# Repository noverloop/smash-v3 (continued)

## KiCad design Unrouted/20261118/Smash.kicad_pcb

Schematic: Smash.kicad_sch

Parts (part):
CBAT1, CBAT2: 100uF; Capacitor_Tantalum_SMD_CP_EIA-7343-15_Kemet-W; MPN T528W 100uF (7343-15 thinnest variant)
CBAT3: 1uF; Capacitor_SMD_C_0805_2012Metric; MPN C-Series MIL-PRF-32535 X7R 0805 1uF
CBOOST_IN1_1, CBOOST_IN1_2, CBOOST_IN1_3, CBOOST_IN1_4, CBOOST_IN1_5: 2.2uF; Capacitor_SMD_C_0603_1608Metric; MPN C-Series MIL-PRF-32535 X7R 0603 2.2uF
CBOOST_IN2: 100nF; Capacitor_SMD_C_0402_1005Metric; MPN C0402 X7R 100nF
CBOOST_OUT1: 22uF; Capacitor_Tantalum_SMD_CP_EIA-3528-12_Kemet-T; MPN T491T 22uF (3528-12 thinnest variant)
CBOOST_OUT2: 100nF; Capacitor_SMD_C_0402_1005Metric; MPN C0402 X7R 100nF
CMAIN_HOLD1: 100nF; Capacitor_SMD_C_0402_1005Metric; MPN C0402 X7R 100nF
COUT1, COUT2: 22uF; Capacitor_Tantalum_SMD_CP_EIA-3528-12_Kemet-T; MPN T491T 22uF (3528-12 thinnest variant)
COUT3: 100nF; Capacitor_SMD_C_0402_1005Metric; MPN C0402 X7R 100nF
C_ACTIVATE_COMP1: 220nF; Capacitor_SMD_C_0603_1608Metric; MPN C-Series MIL-PRF-32535 X7R 0603 220nF
C_ACTIVATE_IN_1, C_ACTIVATE_IN_2, C_ACTIVATE_IN_3, C_ACTIVATE_IN_4, C_ACTIVATE_IN_5: 2.2uF; Capacitor_SMD_C_0603_1608Metric; MPN C-Series MIL-PRF-32535 X7R 0603 2.2uF
C_ACTIVATE_OUT_1, C_ACTIVATE_OUT_2: 2.2uF; Capacitor_SMD_C_0603_1608Metric; MPN C-Series MIL-PRF-32535 X7R 0603 2.2uF
C_ACTIVATE_SS1: 47nF; Capacitor_SMD_C_0402_1005Metric; MPN C0402 X7R 47nF
C_ANTSW_S1_VDD1: 100nF; Capacitor_SMD_C_0402_1005Metric; MPN C0402 X7R 100nF
C_ANT_S1_DCBLK1: 100pF; Capacitor_SMD_C_0402_1005Metric; MPN TBD 0402 C0G/NP0 100pF (as placed; conf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
C_ANT_S4_MATCH1: 0.5pF; Capacitor_SMD_C_0402_1005Metric; MPN TBD 0402 C0G/NP0 0.5pF (as placed; conf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
C_AON_IN1: 1uF; Capacitor_SMD_C_0805_2012Metric; MPN C-Series MIL-PRF-32535 X7R 0805 1uF
C_AON_OUT1: 1uF; Capacitor_SMD_C_0805_2012Metric; MPN C-Series MIL-PRF-32535 X7R 0805 1uF
C_AWR_1V2_1, C_AWR_1V3_1: 22uF; Capacitor_Tantalum_SMD_CP_EIA-3528-12_Kemet-T; MPN T491T 22uF (3528-12 thinnest variant)
C_AWR_1V2_2, C_AWR_1V3_2, C_AWR_1V8_2, C_AWR_14APLL1, C_AWR_14SYNTH1: 100nF; Capacitor_SMD_C_0402_1005Metric; MPN C0402 X7R 100nF
C_AWR_1V8_1_1, C_AWR_1V8_1_2, C_AWR_1V8_1_3, C_AWR_1V8_1_4, C_AWR_1V8_1_5: 2.2uF; Capacitor_SMD_C_0603_1608Metric; MPN C-Series MIL-PRF-32535 X7R 0603 2.2uF
C_AWR_BUCK_IN1_1, C_AWR_BUCK_IN1_2, C_AWR_BUCK_IN1_3, C_AWR_BUCK_IN1_4, C_AWR_BUCK_IN1_5: 2.2uF; Capacitor_SMD_C_0603_1608Metric; MPN C-Series MIL-PRF-32535 X7R 0603 2.2uF
C_AWR_BUCK_IN2: 100nF; Capacitor_SMD_C_0402_1005Metric; MPN C0402 X7R 100nF
C_AWR_CLKM1: 100pF; Capacitor_SMD_C_0603_1608Metric; MPN SQCSVA 100pF
C_AWR_FLASH_VCC1: 100nF; Capacitor_SMD_C_0402_1005Metric; MPN C0402 X7R 100nF
C_AWR_NRST1: 100nF; Capacitor_SMD_C_0402_1005Metric; MPN C0402 X7R 100nF
C_AWR_OSC_VDD1: 100nF; Capacitor_SMD_C_0402_1005Metric; MPN C0402 X7R 100nF
C_AWR_VBGAP1: 100nF; Capacitor_SMD_C_0402_1005Metric; MPN C0402 X7R 100nF
C_AWR_VOUT_PA1: 100nF; Capacitor_SMD_C_0402_1005Metric; MPN C0402 X7R 100nF
C_BAT_BULK1, C_BAT_BULK2: 470uF; Capacitor_Tantalum_SMD_CP_EIA-7343-15_Kemet-W; MPN T528W 470uF (7343-15 thinnest variant)
C_BLE_DCBLK1: 100pF; Capacitor_SMD_C_0402_1005Metric; MPN TBD 0402 C0G/NP0 100pF (as placed; conf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
C_BOOST_COMP1: 220nF; Capacitor_SMD_C_0603_1608Metric; MPN C-Series MIL-PRF-32535 X7R 0603 220nF
C_BOOST_OUT1: 47uF; Capacitor_Tantalum_SMD_CP_EIA-7343-15_Kemet-W; MPN T528W 47uF (7343-15 thinnest variant)
C_BOOST_OUT2_1, C_BOOST_OUT2_2, C_BOOST_OUT2_3, C_BOOST_OUT2_4, C_BOOST_OUT2_5: 2.2uF; Capacitor_SMD_C_0603_1608Metric; MPN C-Series MIL-PRF-32535 X7R 0603 2.2uF
C_BOOST_OUT3: 100nF; Capacitor_SMD_C_0402_1005Metric; MPN C0402 X7R 100nF
C_BOOST_SS1: 47nF; Capacitor_SMD_C_0402_1005Metric; MPN C0402 X7R 47nF
C_CAM_LDO_VAA_IN1: 1uF; Capacitor_SMD_C_0805_2012Metric; MPN C-Series MIL-PRF-32535 X7R 0805 1uF
C_CAM_LDO_VAA_OUT_1, C_CAM_LDO_VAA_OUT_2: 2.2uF; Capacitor_SMD_C_0603_1608Metric; MPN C-Series MIL-PRF-32535 X7R 0603 2.2uF
C_CAM_LDO_VDD_IN1: 1uF; Capacitor_SMD_C_0805_2012Metric; MPN C-Series MIL-PRF-32535 X7R 0805 1uF
C_CAM_LDO_VDD_OUT1: 2.2uF; Capacitor_SMD_C_0603_1608Metric; MPN C-Series MIL-PRF-32535 X7R 0603 2.2uF
C_CAM_PHY_REG1: 1uF; Capacitor_SMD_C_0805_2012Metric; MPN C-Series MIL-PRF-32535 X7R 0805 1uF
C_CAM_VAA_1: 100nF; Capacitor_SMD_C_0402_1005Metric; MPN C0402 X7R 100nF
C_CAM_VAA_BULK1: 1uF; Capacitor_SMD_C_0805_2012Metric; MPN C-Series MIL-PRF-32535 X7R 0805 1uF
C_CAM_VDD1: 100nF; Capacitor_SMD_C_0402_1005Metric; MPN C0402 X7R 100nF
C_CAM_VDDIO_1: 100nF; Capacitor_SMD_C_0402_1005Metric; MPN C0402 X7R 100nF
C_CAM_VDDIO_BULK1: 1uF; Capacitor_SMD_C_0805_2012Metric; MPN C-Series MIL-PRF-32535 X7R 0805 1uF
C_CAM_VDD_1: 100nF; Capacitor_SMD_C_0402_1005Metric; MPN C0402 X7R 100nF
C_CAM_VDD_BULK1: 1uF; Capacitor_SMD_C_0805_2012Metric; MPN C-Series MIL-PRF-32535 X7R 0805 1uF
C_CAN_GW1: 100nF; Capacitor_SMD_C_0402_1005Metric; MPN C0402 X7R 100nF
C_COMP_PZ1: 100nF; Capacitor_SMD_C_0402_1005Metric; MPN C0402 X7R 100nF
C_DDR_BULK1_1, C_DDR_BULK1_2, C_DDR_BULK1_3, C_DDR_BULK1_4, C_DDR_BULK1_5, C_DDR_BULK2_1, C_DDR_BULK2_2, C_DDR_BULK2_3, C_DDR_BULK2_4, C_DDR_BULK2_5: 2.2uF; Capacitor_SMD_C_0603_1608Metric; MPN C-Series MIL-PRF-32535 X7R 0603 2.2uF
C_DDR_VDD1, C_DDR_VDD2, C_DDR_VDD3, C_DDR_VDD4, C_DDR_VDD5, C_DDR_VDD6: 100nF; Capacitor_SMD_C_0402_1005Metric; MPN C0402 X7R 100nF
C_DDR_VPP1: 1uF; Capacitor_SMD_C_0805_2012Metric; MPN C-Series MIL-PRF-32535 X7R 0805 1uF
C_DDR_VPP2: 100nF; Capacitor_SMD_C_0402_1005Metric; MPN C0402 X7R 100nF
C_DDR_VREFCA1: 100nF; Capacitor_SMD_C_0402_1005Metric; MPN C0402 X7R 100nF
C_FIN1_DVDD1, C_FIN2_DVDD1, C_FIN3_DVDD1, C_FIN4_DVDD1: 1uF; Capacitor_SMD_C_0805_2012Metric; MPN C-Series MIL-PRF-32535 X7R 0805 1uF
C_FIN1_VM1, C_FIN2_VM1, C_FIN3_VM1, C_FIN4_VM1: 100nF; Capacitor_SMD_C_0402_1005Metric; MPN C0402 X7R 100nF
C_FIN_VM_BULK_1, C_FIN_VM_BULK_2, C_FIN_VM_BULK_3, C_FIN_VM_BULK_4, C_FIN_VM_BULK_5: 2.2uF; Capacitor_SMD_C_0603_1608Metric; MPN C-Series MIL-PRF-32535 X7R 0603 2.2uF
C_FIN_VREF1: 100nF; Capacitor_SMD_C_0402_1005Metric; MPN C0402 X7R 100nF
C_G0B1_FIN_BULK1: 1uF; Capacitor_SMD_C_0805_2012Metric; MPN C-Series MIL-PRF-32535 X7R 0805 1uF
C_G0B1_FIN_NRST1, C_G0B1_FIN_VDD1, C_G0B1_FIN_VDD2, C_G0B1_FIN_VREF1: 100nF; Capacitor_SMD_C_0402_1005Metric; MPN C0402 X7R 100nF
C_HACC1: 100nF; Capacitor_SMD_C_0402_1005Metric; MPN C0402 X7R 100nF
C_HACC2_1, C_HACC2_2, C_HACC2_3, C_HACC2_4, C_HACC2_5: 2.2uF; Capacitor_SMD_C_0603_1608Metric; MPN C-Series MIL-PRF-32535 X7R 0603 2.2uF
C_IMU1_1, C_IMU2_1, C_IMU3_1: 100nF; Capacitor_SMD_C_0402_1005Metric; MPN C0402 X7R 100nF
C_IMU1_2, C_IMU2_2, C_IMU3_2: 2.2uF; Capacitor_SMD_C_0603_1608Metric; MPN C-Series MIL-PRF-32535 X7R 0603 2.2uF
C_IMU1_3, C_IMU2_3, C_IMU3_3: 10nF; Capacitor_SMD_C_0402_1005Metric; MPN C0402 X7R 10nF
C_IR_TX1: 1uF; Capacitor_SMD_C_0805_2012Metric; MPN C-Series MIL-PRF-32535 X7R 0805 1uF
C_IR_WAKE1: 10nF; Capacitor_SMD_C_0402_1005Metric; MPN C0402 X7R 10nF
C_J_HALL_FIN_VCC1: 100nF; Capacitor_SMD_C_0402_1005Metric; MPN C0402 X7R 100nF
C_LR_BULK_1, C_LR_BULK_2: 2.2uF; Capacitor_SMD_C_0603_1608Metric; MPN C-Series MIL-PRF-32535 X7R 0603 2.2uF
C_LR_DTC1_VDD1, C_LR_DTC2_VDD1: 100nF; Capacitor_SMD_C_0402_1005Metric; MPN C0402 X7R 100nF
C_LR_HF_ANTBLK1: 100pF; Capacitor_SMD_C_0402_1005Metric; MPN TBD 0402 C0G/NP0 100pF (as placed; conf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
C_LR_HF_RX1: 0.8pF; Capacitor_SMD_C_0402_1005Metric; MPN TBD 0402 C0G/NP0 0.8pF (as placed; conf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
C_LR_HF_RXBLK1: 100pF; Capacitor_SMD_C_0402_1005Metric; MPN TBD 0402 C0G/NP0 100pF (as placed; conf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
C_LR_HF_TX1: 1.2pF; Capacitor_SMD_C_0402_1005Metric; MPN TBD 0402 C0G/NP0 1.2pF (as placed; conf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
C_LR_HF_TX2: 1.0pF; Capacitor_SMD_C_0402_1005Metric; MPN TBD 0402 C0G/NP0 1.0pF (as placed; conf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
C_LR_HF_TXBLK1: 100pF; Capacitor_SMD_C_0402_1005Metric; MPN TBD 0402 C0G/NP0 100pF (as placed; conf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
C_LR_IFSW_VDD1: 100nF; Capacitor_SMD_C_0402_1005Metric; MPN C0402 X7R 100nF
C_LR_SW_HF_VDD1: 100nF; Capacitor_SMD_C_0402_1005Metric; MPN C0402 X7R 100nF
C_LR_TCXO_AC1: 10pF; Capacitor_SMD_C_0402_1005Metric; MPN TBD 0402 C0G/NP0 10pF (as placed; confi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
C_LR_VBAT1: 100nF; Capacitor_SMD_C_0402_1005Metric; MPN C0402 X7R 100nF
C_LR_VDCC1, C_LR_VDCC2: 1uF; Capacitor_SMD_C_0805_2012Metric; MPN C-Series MIL-PRF-32535 X7R 0805 1uF
C_LR_VPAX1, C_LR_VPAX2: 2.2uF; Capacitor_SMD_C_0603_1608Metric; MPN C-Series MIL-PRF-32535 X7R 0603 2.2uF
C_LR_VRPA1: 1nF; Capacitor_SMD_C_0402_1005Metric; MPN C0402 X7R 1nF
C_LR_VTCXO1: 100nF; Capacitor_SMD_C_0402_1005Metric; MPN C0402 X7R 100nF
C_MAG1: 100nF; Capacitor_SMD_C_0402_1005Metric; MPN C0402 X7R 100nF
C_MAG2: 1uF; Capacitor_SMD_C_0805_2012Metric; MPN C-Series MIL-PRF-32535 X7R 0805 1uF
C_MAG_C1: 220nF; Capacitor_SMD_C_0603_1608Metric; MPN C-Series MIL-PRF-32535 X7R 0603 220nF
C_MAG_SHELF1: 100nF; Capacitor_SMD_C_0402_1005Metric; MPN C0402 X7R 100nF
C_MAG_WAKE1: 100nF; Capacitor_SMD_C_0402_1005Metric; MPN C0402 X7R 100nF
C_MPU_0V82_1, C_MPU_0V82_2, C_MPU_5V2, C_MPU_18A_1, C_MPU_18A_2, C_MPU_33b1: 100nF; Capacitor_SMD_C_0402_1005Metric; MPN C0402 X7R 100nF
C_MPU_0V82_BULK1, C_MPU_5V_1, C_MPU_5V_2, C_MPU_5V_3, C_MPU_5V_4, C_MPU_5V_5, C_MPU_33_1, C_MPU_33_2, C_MPU_33_3, C_MPU_33_4, C_MPU_33_5: 2.2uF; Capacitor_SMD_C_0603_1608Metric; MPN C-Series MIL-PRF-32535 X7R 0603 2.2uF
C_MPU_DDR_ZQ1: 0.1uF; Capacitor_SMD_C_0402_1005Metric; MPN C0402 X7R 0.1uF
C_MPU_HSE_VDD1: 100nF; Capacitor_SMD_C_0402_1005Metric; MPN C0402 X7R 100nF
C_MPU_LSE_VDD1: 100nF; Capacitor_SMD_C_0402_1005Metric; MPN C0402 X7R 100nF
C_MPU_NRST1: 100nF; Capacitor_SMD_C_0402_1005Metric; MPN C0402 X7R 100nF
C_MPU_QDDR_1, C_MPU_QDDR_2: 100nF; Capacitor_SMD_C_0402_1005Metric; MPN C0402 X7R 100nF
C_MPU_V08CAP1: 2.2uF; Capacitor_SMD_C_0603_1608Metric; MPN C-Series MIL-PRF-32535 X7R 0603 2.2uF
C_NAND_A_BULK1: 1uF; Capacitor_SMD_C_0805_2012Metric; MPN C-Series MIL-PRF-32535 X7R 0805 1uF
C_NAND_A_VCC1: 100nF; Capacitor_SMD_C_0402_1005Metric; MPN C0402 X7R 100nF
C_NAND_B_BULK1: 1uF; Capacitor_SMD_C_0805_2012Metric; MPN C-Series MIL-PRF-32535 X7R 0805 1uF
C_NAND_B_VCC1: 100nF; Capacitor_SMD_C_0402_1005Metric; MPN C0402 X7R 100nF
C_PMIC_0V9_1, C_PMIC_0V82_1, C_PMIC_1V8_1, C_PMIC_3V3_1: 22uF; Capacitor_Tantalum_SMD_CP_EIA-3528-12_Kemet-T; MPN T491T 22uF (3528-12 thinnest variant)
C_PMIC_0V9_2, C_PMIC_0V82_2, C_PMIC_1V2_2, C_PMIC_1V8_2, C_PMIC_2V8_2, C_PMIC_3V3_2: 100nF; Capacitor_SMD_C_0402_1005Metric; MPN C0402 X7R 100nF
C_PMIC_1V2_1_1, C_PMIC_1V2_1_2, C_PMIC_1V2_1_3, C_PMIC_1V2_1_4, C_PMIC_1V2_1_5, C_PMIC_2V8_1_1, C_PMIC_2V8_1_2, C_PMIC_5V_FILT_1, C_PMIC_5V_FILT_2, C_PMIC_5V_FILT_3, C_PMIC_5V_FILT_4, C_PMIC_5V_FILT_5: 2.2uF; Capacitor_SMD_C_0603_1608Metric; MPN C-Series MIL-PRF-32535 X7R 0603 2.2uF
C_PMIC_INTLDO_1, C_PMIC_INTLDO_2: 2.2uF; Capacitor_SMD_C_0603_1608Metric; MPN C-Series MIL-PRF-32535 X7R 0603 2.2uF
C_PMIC_LDO1, C_PMIC_LDO2, C_PMIC_LDO4, C_PMIC_LDO6, C_PMIC_LDO7, C_PMIC_LDO8: 100nF; Capacitor_SMD_C_0402_1005Metric; MPN C0402 X7R 100nF
C_PMIC_VIN1: 22uF; Capacitor_Tantalum_SMD_CP_EIA-3528-12_Kemet-T; MPN T491T 22uF (3528-12 thinnest variant)
C_PMIC_VIN2: 100nF; Capacitor_SMD_C_0402_1005Metric; MPN C0402 X7R 100nF
C_PMIC_VIN3, C_PMIC_VIN4, C_PMIC_VIN5, C_PMIC_VIN6: 2.2uF; Capacitor_SMD_C_0603_1608Metric; MPN C-Series MIL-PRF-32535 X7R 0603 2.2uF
C_PMIC_VLX7: 100nF; Capacitor_SMD_C_0402_1005Metric; MPN C0402 X7R 100nF
C_PMIC_VOUT7: 100nF; Capacitor_SMD_C_0402_1005Metric; MPN C0402 X7R 100nF
C_PMIC_VPP_1: 22uF; Capacitor_Tantalum_SMD_CP_EIA-3528-12_Kemet-T; MPN T491T 22uF (3528-12 thinnest variant)
C_PMIC_VPP_2: 100nF; Capacitor_SMD_C_0402_1005Metric; MPN C0402 X7R 100nF
C_QPD_VREF1: 1uF; Capacitor_SMD_C_0805_2012Metric; MPN C-Series MIL-PRF-32535 X7R 0805 1uF
C_QPD_VREF2: 100nF; Capacitor_SMD_C_0402_1005Metric; MPN C0402 X7R 100nF
C_TIA_A1: 8.2pF; Capacitor_SMD_C_0603_1608Metric; MPN SQCSVA 8.2pF
C_TIA_A_PWR1: 100nF; Capacitor_SMD_C_0402_1005Metric; MPN C0402 X7R 100nF
C_TIA_B1: 8.2pF; Capacitor_SMD_C_0603_1608Metric; MPN SQCSVA 8.2pF
C_TIA_B_PWR1: 100nF; Capacitor_SMD_C_0402_1005Metric; MPN C0402 X7R 100nF
C_TIA_C1: 8.2pF; Capacitor_SMD_C_0603_1608Metric; MPN SQCSVA 8.2pF
C_TIA_C_PWR1: 100nF; Capacitor_SMD_C_0402_1005Metric; MPN C0402 X7R 100nF
C_TIA_D1: 8.2pF; Capacitor_SMD_C_0603_1608Metric; MPN SQCSVA 8.2pF
C_TIA_D_PWR1: 100nF; Capacitor_SMD_C_0402_1005Metric; MPN C0402 X7R 100nF
C_TMP1: 100nF; Capacitor_SMD_C_0402_1005Metric; MPN C0402 X7R 100nF
C_TMR_LDO1: 1uF; Capacitor_SMD_C_0805_2012Metric; MPN C-Series MIL-PRF-32535 X7R 0805 1uF
C_USB_18: 100nF; Capacitor_SMD_C_0402_1005Metric; MPN C0402 X7R 100nF
C_USB_33: 1uF; Capacitor_SMD_C_0805_2012Metric; MPN C-Series MIL-PRF-32535 X7R 0805 1uF
C_USB_VBUS_1, C_USB_VBUS_2, C_USB_VBUS_3, C_USB_VBUS_4, C_USB_VBUS_5: 2.2uF; Capacitor_SMD_C_0603_1608Metric; MPN C-Series MIL-PRF-32535 X7R 0603 2.2uF
C_WBA_BULK_1, C_WBA_BULK_2: 2.2uF; Capacitor_SMD_C_0603_1608Metric; MPN C-Series MIL-PRF-32535 X7R 0603 2.2uF
C_WBA_HSE_VDD1: 100nF; Capacitor_SMD_C_0402_1005Metric; MPN C0402 X7R 100nF
C_WBA_NRST1: 100nF; Capacitor_SMD_C_0402_1005Metric; MPN C0402 X7R 100nF
C_WBA_PI1: 0.5pF; Capacitor_SMD_C_0402_1005Metric; MPN TBD 0402 C0G/NP0 0.5pF (as placed; conf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
C_WBA_PI2: 0.5pF; Capacitor_SMD_C_0603_1608Metric; MPN SQCSVA 0.5pF
C_WBA_VDD1, C_WBA_VDD2, C_WBA_VDD3, C_WBA_VDD4: 100nF; Capacitor_SMD_C_0402_1005Metric; MPN C0402 X7R 100nF
C_WBA_VDD11: 2.2uF; Capacitor_SMD_C_0402_1005Metric; MPN TBD 0402 X5R 2.2uF (as placed; confirm 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
C_WBA_VDDA1: 100nF; Capacitor_SMD_C_0402_1005Metric; MPN C0402 X7R 100nF
C_WBA_VDDANA1: 100nF; Capacitor_SMD_C_0402_1005Metric; MPN C0402 X7R 100nF
C_WBA_VDDHPA1: 100nF; Capacitor_SMD_C_0402_1005Metric; MPN C0402 X7R 100nF
C_WBA_VDDRF1: 100nF; Capacitor_SMD_C_0402_1005Metric; MPN C0402 X7R 100nF
C_WBA_VDDRFPA1: 100nF; Capacitor_SMD_C_0402_1005Metric; MPN C0402 X7R 100nF
C_WBA_VDDSMPS1: 100nF; Capacitor_SMD_C_0402_1005Metric; MPN C0402 X7R 100nF
C_XV_BPF_SER1: 0.5pF; Capacitor_SMD_C_0402_1005Metric; MPN TBD 0402 C0G/NP0 0.5pF (as placed; conf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
C_XV_BPF_SH1: 1.1pF; Capacitor_SMD_C_0402_1005Metric; MPN TBD 0402 C0G/NP0 1.1pF (as placed; conf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
C_XV_BST_IN_1, C_XV_BST_IN_2, C_XV_BST_IN_3, C_XV_BST_IN_4, C_XV_BST_IN_5: 2.2uF; Capacitor_SMD_C_0603_1608Metric; MPN C-Series MIL-PRF-32535 X7R 0603 2.2uF
C_XV_BST_OUT1: 22uF; Capacitor_Tantalum_SMD_CP_EIA-3528-12_Kemet-T; MPN T491T 22uF (3528-12 thinnest variant)
C_XV_LNA_IN1: 1.2pF; Capacitor_SMD_C_0402_1005Metric; MPN TBD 0402 C0G/NP0 1.2pF (as placed; conf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
C_XV_LNA_OUT1: 5.1pF; Capacitor_SMD_C_0402_1005Metric; MPN TBD 0402 C0G/NP0 5.1pF (as placed; conf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
C_XV_LNA_VDD1: 100nF; Capacitor_SMD_C_0402_1005Metric; MPN C0402 X7R 100nF
C_XV_LNA_VDD2: 100pF; Capacitor_SMD_C_0402_1005Metric; MPN TBD 0402 C0G/NP0 100pF (as placed; conf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
C_XV_LO_AVDD1: 100nF; Capacitor_SMD_C_0402_1005Metric; MPN C0402 X7R 100nF
C_XV_LO_BULK_1, C_XV_LO_BULK_2, C_XV_LO_BULK_3, C_XV_LO_BULK_4, C_XV_LO_BULK_5: 2.2uF; Capacitor_SMD_C_0603_1608Metric; MPN C-Series MIL-PRF-32535 X7R 0603 2.2uF
C_XV_LO_DVDD1: 100nF; Capacitor_SMD_C_0402_1005Metric; MPN C0402 X7R 100nF
C_XV_LO_LF1: 1nF; Capacitor_SMD_C_0402_1005Metric; MPN TBD 0402 C0G/NP0 1nF (as placed; confir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
C_XV_LO_LF2: 22nF; Capacitor_SMD_C_0402_1005Metric; MPN C0402 X7R 22nF
C_XV_LO_LF3: 220pF; Capacitor_SMD_C_0402_1005Metric; MPN TBD 0402 C0G/NP0 220pF (as placed; conf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
C_XV_LO_OUTN1: 100pF; Capacitor_SMD_C_0402_1005Metric; MPN TBD 0402 C0G/NP0 100pF (as placed; conf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
C_XV_LO_OUTP1: 100pF; Capacitor_SMD_C_0402_1005Metric; MPN TBD 0402 C0G/NP0 100pF (as placed; conf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
C_XV_LO_REF1: 100pF; Capacitor_SMD_C_0402_1005Metric; MPN TBD 0402 C0G/NP0 100pF (as placed; conf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
C_XV_LO_SDVDD1: 100nF; Capacitor_SMD_C_0402_1005Metric; MPN C0402 X7R 100nF
C_XV_LO_TEMP1: 100nF; Capacitor_SMD_C_0402_1005Metric; MPN C0402 X7R 100nF
C_XV_LO_VCOM1: 100nF; Capacitor_SMD_C_0402_1005Metric; MPN C0402 X7R 100nF
C_XV_LO_VP1: 100nF; Capacitor_SMD_C_0402_1005Metric; MPN C0402 X7R 100nF
C_XV_LO_VREF1: 100nF; Capacitor_SMD_C_0402_1005Metric; MPN C0402 X7R 100nF
C_XV_LO_VVCO1: 100nF; Capacitor_SMD_C_0402_1005Metric; MPN C0402 X7R 100nF
C_XV_LO_VVCO_2: 100nF; Capacitor_SMD_C_0402_1005Metric; MPN C0402 X7R 100nF
C_XV_MIX_IF1: 100pF; Capacitor_SMD_C_0402_1005Metric; MPN TBD 0402 C0G/NP0 100pF (as placed; conf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
C_XV_MIX_LO1: 100pF; Capacitor_SMD_C_0402_1005Metric; MPN TBD 0402 C0G/NP0 100pF (as placed; conf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
C_XV_MIX_RF1: 10pF; Capacitor_SMD_C_0402_1005Metric; MPN TBD 0402 C0G/NP0 10pF (as placed; confi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
C_XV_MIX_VCC1: 1uF; Capacitor_SMD_C_0805_2012Metric; MPN C-Series MIL-PRF-32535 X7R 0805 1uF
C_XV_MIX_VCC2: 1nF; Capacitor_SMD_C_0402_1005Metric; MPN TBD 0402 C0G/NP0 1nF (as placed; confir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
C_XV_PA_BULK1_1, C_XV_PA_BULK1_2, C_XV_PA_BULK1_3, C_XV_PA_BULK1_4, C_XV_PA_BULK1_5: 2.2uF; Capacitor_SMD_C_0603_1608Metric; MPN C-Series MIL-PRF-32535 X7R 0603 2.2uF
C_XV_PA_CHOKE1: 100nF; Capacitor_SMD_C_0402_1005Metric; MPN C0402 X7R 100nF
C_XV_PA_IN1: 1.5pF; Capacitor_SMD_C_0402_1005Metric; MPN TBD 0402 C0G/NP0 1.5pF (as placed; conf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
C_XV_PA_OUT1: 10pF; Capacitor_SMD_C_0402_1005Metric; MPN TBD 0402 C0G/NP0 10pF (as placed; confi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
C_XV_PA_OUTSH1: 0.8pF; Capacitor_SMD_C_0402_1005Metric; MPN TBD 0402 C0G/NP0 0.8pF (as placed; conf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
C_XV_PA_VB1, C_XV_PA_VB2: 100nF; Capacitor_SMD_C_0402_1005Metric; MPN C0402 X7R 100nF
C_XV_PA_VDD1: 100nF; Capacitor_SMD_C_0402_1005Metric; MPN C0402 X7R 100nF
C_XV_TR1_VDD1, C_XV_TR2_VDD1: 100nF; Capacitor_SMD_C_0402_1005Metric; MPN C0402 X7R 100nF
D_ACTIVATE1: MBRS540T3G; DIOM7958X256N; MPN MBRS540T3G
D_AON_WAKE1: BAT64-06-TP; SOT95P237X125-3N; MPN BAT64-06-TP
D_AWR_BUCK12, D_AWR_BUCK13: MBRS340T3G; DIOM8059X261N; MPN MBRS340T3G
D_BOOST_COMP1: PMEG040V050EPE-QZ; PMEG040V050EPEQZ; MPN PMEG040V050EPE-QZ
D_IR_TX1: VSMB1940X01; MPN VSMB1940X01
D_IR_WAKE1: VBPW34FAS; MPN VBPW34FAS
D_JUMP_WAKE1: BAT64-06-TP; SOT95P237X125-3N; MPN BAT64-06-TP
FB_LR_VBAT1: 220R@100MHz; BLM18SP221SN1B; MPN BLM18PG221SN1D
FB_XV_LO1: 220R@100MHz; BLM18SP221SN1B; MPN BLM18PG221SN1D
J_CAST_activation_interface1: CASTELLATIONS; Castellations_activation_interface; MPN CASTELLATIONS
J_CAST_aft_end_board1: CASTELLATIONS; Castellations_aft_end_board; MPN CASTELLATIONS
J_CAST_camera_module1: CASTELLATIONS; Castellations_camera_module; MPN CASTELLATIONS
J_CAST_companion_compute1: CASTELLATIONS; Castellations_companion_compute; MPN CASTELLATIONS
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
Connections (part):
3V3: COUT1.1 (+), COUT2.1 (+), COUT3.1, C_G0B1_FIN_BULK1.1, C_G0B1_FIN_VDD1.1, C_G0B1_FIN_VDD2.1, C_G0B1_FIN_VREF1.1, C_HACC1.1, C_HACC2_1.1, C_HACC2_2.1, C_HACC2_3.1, C_HACC2_4.1, C_HACC2_5.1, C_IMU1_1.1, C_IMU1_2.1, C_IMU1_3.1, C_IMU2_1.1, C_IMU2_2.1, C_IMU2_3.1, C_IMU3_1.1, C_IMU3_2.1, C_IMU3_3.1, C_J_HALL_FIN_VCC1.1, C_LR_DTC1_VDD1.1, C_LR_DTC2_VDD1.1, C_LR_IFSW_VDD1.1, C_LR_SW_HF_VDD1.1, C_MAG1.1, C_MAG2.1, C_TIA_A_PWR1.1, C_TIA_B_PWR1.1, C_TIA_C_PWR1.1, C_TIA_D_PWR1.1, C_TMP1.1, C_XV_BST_IN_1.1, C_XV_BST_IN_2.1, C_XV_BST_IN_3.1, C_XV_BST_IN_4.1, C_XV_BST_IN_5.1, C_XV_MIX_VCC1.1, C_XV_MIX_VCC2.1, C_XV_TR1_VDD1.1, C_XV_TR2_VDD1.1, FB_LR_VBAT1.1, FB_XV_LO1.1, J_CAST_aft_end_board1.63 (3V3@357.293deg), J_CAST_companion_compute1.43 (CONE:qpd_module:3V3@178.647deg), J_CAST_companion_compute1.80 (3V3@357.293deg), J_CAST_fin_ble_board1.40 (3V3@357.293deg), J_CAST_power_board1.28 (3V3@357.293deg), J_CAST_qpd_module1.7 (CONE:qpd_module:3V3@178.647deg), J_CAST_wakeup_board1.34 (3V3@357.293deg), J_HALL_FIN_VCC1.1, L_XV_BOOST1.1, RPU_I2C2_SCL1.1, RPU_I2C2_SDA1.1, RPU_I2C3_SCL1.1, RPU_I2C3_SDA1.1, RPU_SCL_EXT1.1, RPU_SDA_EXT1.1, R_G0B1_FIN_NRST1.1, R_IMU1_SCX_PU1.1, R_IMU1_SDX_PU1.1, R_IMU2_SCX_PU1.1, R_IMU2_SDX_PU1.1, R_IMU3_SCX_PU1.1, R_IMU3_SDX_PU1.1, R_J_HALL_FIN_PU1.1, R_LR_NSS_PU1.1, R_PMIC_NRST1.1, R_PMIC_PONKEY1.1, R_PMIC_PWR_OK1.1, R_PMIC_WAKEUP1.1, R_QPD_VREF_H1.1, R_XV_LNA_VDD1.1, TP_3V3.1, TP_HALL_VIN1.1, U_CAN_GW1.5 (VIO), U_G0B1_FIN1.D1 (VDD/_VDDA), U_G0B1_FIN1.D2 (VREF+)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
3V3_AON: C_ANTSW_S1_VDD1.1, C_AON_OUT1.1, C_COMP_PZ1.1, C_MAG_WAKE1.1, C_WBA_BULK_1.1, C_WBA_BULK_2.1, C_WBA_HSE_VDD1.1, C_WBA_VDD1.1, C_WBA_VDD2.1, C_WBA_VDD3.1, C_WBA_VDD4.1, C_WBA_VDDA1.1, C_WBA_VDDANA1.1, C_WBA_VDDHPA1.1, C_WBA_VDDRF1.1, C_WBA_VDDRFPA1.1, C_WBA_VDDSMPS1.1, J_CAST_aft_end_board1.53 (3V3_AON@330.226deg), J_CAST_wakeup_board1.31 (3V3_AON@330.226deg), RPU_IR_WAKE1.1, RPU_MAG_WAKE1.1, R_THR1.1, R_WBA_NRST1.1, TP_VDD1.1, U_ANTSW_S1.4 (VDD), U_AON_LDO1.5 (OUT), U_COMP_PZ1.6 (VCC), U_MAG_WAKE1.1 (VCC), U_WBA1.A4 (VDD_RFPA), U_WBA1.A6 (VDDRF), U_WBA1.B1 (VDD_SMPS), U_WBA1.B4 (VDD_HPA), U_WBA1.B6 (VDD_ANA), U_WBA1.C6 (VDD_1), U_WBA1.D6 (VDD_2), U_WBA1.E4 (VDD_3), U_WBA1.F1 (VDDA), U_WBA1.F5 (VDD_4), Y_WBA_HSE1.1 (STANDBY#), Y_WBA_HSE1.4 (VDD)
ACTIVATE_COMP: R_ACTIVATE_COMP1.1, U_ACTIVATE_BOOST1.8 (COMP)
ACTIVATE_COMP_C: C_ACTIVATE_COMP1.1, R_ACTIVATE_COMP1.2
ACTIVATE_CONFIRM: J_CAST_activation_interface1.2 (ACTIVATE_CONFIRM@2.707deg), J_CAST_aft_end_board1.2 (ACTIVATE_CONFIRM@2.707deg), J_CAST_companion_compute1.1 (ACTIVATE_CONFIRM@2.707deg), R_ACTIVATE_MON1.2, R_ACTIVATE_MON2.1, TP_ACT_CONFIRM1.1, U_MPU1.C10 (PD9)
ACTIVATE_FB: R_ACTIVATE_FB1.2, R_ACTIVATE_FB2.1, U_ACTIVATE_BOOST1.9 (FB)
ACTIVATE_FREQ: R_ACTIVATE_FREQ1.1, U_ACTIVATE_BOOST1.10 (FREQ)
ACTIVATE_HV: C_ACTIVATE_OUT_1.1, C_ACTIVATE_OUT_2.1, D_ACTIVATE1.1 (K), Q_PARACHUTE_CUTTER_ACTIVATE1.4 (S), R_ACTIVATE_BLEED1.1, R_ACTIVATE_FB1.1, R_ACTIVATE_MON1.1, R_PARACHUTE_CUTTER_ACTIVATE_H1.1
ACTIVATE_SS: C_ACTIVATE_SS1.1, U_ACTIVATE_BOOST1.5 (SS)
ACTIVATE_SW: D_ACTIVATE1.2 (A), L_ACTIVATE1.2, U_ACTIVATE_BOOST1.1 (SW_1), U_ACTIVATE_BOOST1.2 (SW_2)
ACT_WIRE_0: J_CAST_activation_interface1.8 (ACT_WIRE_0@35.188deg), J_CAST_aft_end_board1.12 (ACT_WIRE_0@35.188deg), P_ACT_WIRE_0.1, Q_ACTIVATE_N0.3 (D)
ACT_WIRE_1: J_CAST_activation_interface1.30 (ACT_WIRE_1@322.105deg), J_CAST_aft_end_board1.52 (ACT_WIRE_1@322.105deg), P_ACT_WIRE_1.1, Q_ACTIVATE_N1.3 (D)
ACT_WIRE_2: J_CAST_activation_interface1.12 (ACT_WIRE_2@46.015deg), J_CAST_aft_end_board1.16 (ACT_WIRE_2@46.015deg), P_ACT_WIRE_2.1, Q_ACTIVATE_N2.3 (D)
ACT_WIRE_3: J_CAST_activation_interface1.26 (ACT_WIRE_3@311.278deg), J_CAST_aft_end_board1.48 (ACT_WIRE_3@311.278deg), P_ACT_WIRE_3.1, Q_ACTIVATE_N3.3 (D)
ACT_WIRE_4: J_CAST_activation_interface1.25 (ACT_WIRE_4@278.797deg), J_CAST_aft_end_board1.39 (ACT_WIRE_4@278.797deg), P_ACT_WIRE_4.1, Q_ACTIVATE_N4.3 (D)
ACT_WIRE_5: J_CAST_activation_interface1.14 (ACT_WIRE_5@81.203deg), J_CAST_aft_end_board1.28 (ACT_WIRE_5@81.203deg), P_ACT_WIRE_5.1, Q_ACTIVATE_N5.3 (D)
ACT_WIRE_6: J_CAST_activation_interface1.15 (ACT_WIRE_6@83.91deg), J_CAST_aft_end_board1.29 (ACT_WIRE_6@83.91deg), P_ACT_WIRE_6.1, Q_ACTIVATE_N6.3 (D)
ACT_WIRE_7: J_CAST_activation_interface1.24 (ACT_WIRE_7@276.09deg), J_CAST_aft_end_board1.38 (ACT_WIRE_7@276.09deg), P_ACT_WIRE_7.1, Q_ACTIVATE_N7.3 (D)
ACT_WIRE_8: J_CAST_activation_interface1.16 (ACT_WIRE_8@86.617deg), J_CAST_aft_end_board1.30 (ACT_WIRE_8@86.617deg), P_ACT_WIRE_8.1, Q_ACTIVATE_N8.3 (D)
ACT_WIRE_9: J_CAST_activation_interface1.23 (ACT_WIRE_9@273.383deg), J_CAST_aft_end_board1.37 (ACT_WIRE_9@273.383deg), P_ACT_WIRE_9.1, Q_ACTIVATE_N9.3 (D)
ACT_WIRE_10: J_CAST_activation_interface1.9 (ACT_WIRE_10@37.895deg), J_CAST_aft_end_board1.13 (ACT_WIRE_10@37.895deg), P_ACT_WIRE_10.1, Q_ACTIVATE_N10.3 (D)
ACT_WIRE_11: J_CAST_activation_interface1.29 (ACT_WIRE_11@319.398deg), J_CAST_aft_end_board1.51 (ACT_WIRE_11@319.398deg), P_ACT_WIRE_11.1, Q_ACTIVATE_N11.3 (D)
ACT_WIRE_12: J_CAST_activation_interface1.10 (ACT_WIRE_12@40.602deg), J_CAST_aft_end_board1.14 (ACT_WIRE_12@40.602deg), P_ACT_WIRE_12.1, Q_ACTIVATE_N12.3 (D)
ACT_WIRE_13: J_CAST_activation_interface1.28 (ACT_WIRE_13@316.692deg), J_CAST_aft_end_board1.50 (ACT_WIRE_13@316.692deg), P_ACT_WIRE_13.1, Q_ACTIVATE_N13.3 (D)
ACT_WIRE_14: J_CAST_activation_interface1.11 (ACT_WIRE_14@43.308deg), J_CAST_aft_end_board1.15 (ACT_WIRE_14@43.308deg), P_ACT_WIRE_14.1, Q_ACTIVATE_N14.3 (D)
ACT_WIRE_15: J_CAST_activation_interface1.27 (ACT_WIRE_15@313.985deg), J_CAST_aft_end_board1.49 (ACT_WIRE_15@313.985deg), P_ACT_WIRE_15.1, Q_ACTIVATE_N15.3 (D)
ANTSW_S1_LR: R_ANTSW_S1_PD1.1, U_ANTSW_S1.6 (CTRL), U_LR1.9 (DIO9)
ANT_HF_S1: C_ANT_S1_DCBLK1.2, J_CAST_wakeup_board1.16 (ANT_HF_S1@129.4deg)
ANT_HF_S4: C_ANT_S4_MATCH1.2, J_CAST_wakeup_board1.19 (ANT_HF_S4@149.5deg)
ANT_S1_COM: C_ANT_S1_DCBLK1.1, U_ANTSW_S1.5 (RFIN)
AON_EN: Q_AON_EN1.3 (D), RHOLD_AON1.2, U_AON_LDO1.3 (EN)
AON_EN_GATE: D_AON_WAKE1.3 (COM_A), Q_AON_EN1.1 (G), Q_USB_WAKE2.3 (D), RAON_PU1.2
AWR_1V2: C_AWR_1V2_1.1, C_AWR_1V2_2.1, L_AWR_BUCK12.2, R_AWR12_FB1.1, U_AWR1.A5 (VIN_SRAM_1), U_AWR1.C1 (VNWA_1), U_AWR1.E1 (VDDIN_1), U_AWR1.J1 (VDDIN_2), U_AWR1.V4 (VDDIN_3), U_AWR1.V6 (VIN_SRAM_2), U_AWR1.V7 (VNWA_2), U_AWR1.V8 (VDDIN_4), U_AWR1.V12 (VIN_SRAM_3), U_AWR1.V14 (VNWA_3), U_AWR1.V15 (VDDIN_5)
AWR_1V2_FB: R_AWR12_FB1.2, R_AWR12_FB2.1, U_AWR_BUCK12.3 (FB)
AWR_1V2_SW: D_AWR_BUCK12.1 (K), L_AWR_BUCK12.1, U_AWR_BUCK12.1 (SW)
AWR_1V3: C_AWR_1V3_1.1, C_AWR_1V3_2.1, L_AWR_BUCK13.2, R_AWR13_FB1.1, U_AWR1.H16 (VIN_13RF2_1), U_AWR1.H17 (VIN_13RF2_2), U_AWR1.H18 (VIN_13RF2_3), U_AWR1.J16 (VIN_13RF1_1), U_AWR1.J17 (VIN_13RF1_2), U_AWR1.J18 (VIN_13RF1_3)
AWR_1V3_FB: R_AWR13_FB1.2, R_AWR13_FB2.1, U_AWR_BUCK13.3 (FB)
AWR_1V3_SW: D_AWR_BUCK13.1 (K), L_AWR_BUCK13.1, U_AWR_BUCK13.1 (SW)
AWR_1V8: C_AWR_1V8_1_1.1, C_AWR_1V8_1_2.1, C_AWR_1V8_1_3.1, C_AWR_1V8_1_4.1, C_AWR_1V8_1_5.1, C_AWR_1V8_2.1, C_AWR_OSC_VDD1.1, U_AWR1.A12 (VIN_18VCO_1), U_AWR1.B1 (VIOIN_18_1), U_AWR1.C11 (VIN_18VCO_2), U_AWR1.C15 (VIN_18CLK_1), U_AWR1.C18 (VIN_18CLK_2), U_AWR1.F1 (VIOIN_18_2), U_AWR1.K1 (VIOIN_18_3), U_AWR1.M16 (VIN_18BB_1), U_AWR1.M17 (VIN_18BB_2), U_AWR1.M18 (VIN_18BB_3), U_AWR1.U2 (VIOIN_18DIFF), U_AWR1.V11 (VIOIN_18_4), U_AWR_LDO18.4 (VOUT), Y_AWR_HSE1.1 (STANDBY#), Y_AWR_HSE1.4 (VDD)
AWR_CLKM: C_AWR_CLKM1.1, U_AWR1.B7 (CLKM)
AWR_CLKREF: R_AWR_CLK_SER1.2, R_AWR_CLK_SH1.1, U_AWR1.A7 (CLKP)
AWR_DRDY: J_CAST_companion_compute1.10 (AWR_DRDY@27.068deg), J_CAST_radar_module1.2 (AWR_DRDY@27.068deg), R_AWR_DRDY_PU1.2, U_AWR1.B2 (SPI_HOST_INTR), U_MPU1.U8 (PF1)
AWR_FAULT: J_CAST_companion_compute1.69 (AWR_FAULT@327.519deg), J_CAST_radar_module1.18 (AWR_FAULT@327.519deg), R_AWR_FAULT_PU1.2, U_AWR1.U15 (NERROR_OUT), U_MPU1.D5 (PI7)
AWR_NERR_IN: R_AWR_NERRIN_PU1.2, U_AWR1.U14 (NERROR_IN)
AWR_NRESET: C_AWR_NRST1.1, J_CAST_companion_compute1.12 (AWR_NRESET@32.481deg), J_CAST_radar_module1.3 (AWR_NRESET@32.481deg), R_AWR_NRST1.2, U_AWR1.U11 (NRESET), U_MPU1.D4 (PI6)
AWR_OSC_OUT: R_AWR_CLK_SER1.1, Y_AWR_HSE1.3 (OUT)
AWR_QSPI_CLK: U_AWR1.H2 (QSPI_CLK), U_AWR_FLASH1.6 (SCK)
AWR_QSPI_CS: U_AWR1.J2 (QSPI_CS_N), U_AWR_FLASH1.1 (CE#)
AWR_QSPI_SI: U_AWR1.H3 (QSPI[0]), U_AWR_FLASH1.5 (SI/SIO0)
AWR_QSPI_SO: U_AWR1.G2 (QSPI[1]), U_AWR_FLASH1.2 (SO/SIO1)
AWR_SOP0: R_AWR_SOP0.2, U_AWR1.U10 (TDO)
AWR_SOP1: R_AWR_SOP1.1, U_AWR1.M3 (SYNC_OUT)
AWR_SOP2: R_AWR_SOP2.1, U_AWR1.V10 (PMIC_CLKOUT)
AWR_SPI_CLK: J_CAST_companion_compute1.68 (AWR_SPI_CLK@324.812deg), J_CAST_radar_module1.17 (AWR_SPI_CLK@324.812deg), U_AWR1.D2 (SPIA_CLK), U_MPU1.B10 (PD11)
AWR_SPI_CS: J_CAST_companion_compute1.56 (AWR_SPI_CS@289.624deg), J_CAST_radar_module1.15 (AWR_SPI_CS@289.624deg), U_AWR1.C2 (SPIA_CS_N), U_MPU1.A10 (PD2)
AWR_SPI_MISO: J_CAST_companion_compute1.24 (AWR_SPI_MISO@70.376deg), J_CAST_radar_module1.6 (AWR_SPI_MISO@70.376deg), U_AWR1.D1 (SPIA_MISO), U_MPU1.A14 (PE2)
AWR_SPI_MOSI: J_CAST_companion_compute1.25 (AWR_SPI_MOSI@73.083deg), J_CAST_radar_module1.7 (AWR_SPI_MOSI@73.083deg), U_AWR1.F2 (SPIA_MOSI), U_MPU1.B14 (PE4)
AWR_VOUT_14APLL: C_AWR_14APLL1.1, U_AWR1.A10 (VOUT_14APLL)
AWR_VOUT_14SYNTH: C_AWR_14SYNTH1.1, U_AWR1.A9 (VOUT_14SYNTH)
AWR_VOUT_PA: C_AWR_VOUT_PA1.1, U_AWR1.G16 (VOUT_PA_1), U_AWR1.G17 (VOUT_PA_2), U_AWR1.G18 (VOUT_PA_3)
AWR_WARM_RST: R_AWR_WARMRST_PU1.2, U_AWR1.U13 (WARM_RESET)
BAT_CELL1_POS: J_CAST_activation_interface1.32 (BAT_CELL1_POS@327.519deg), J_CAST_power_board1.26 (BAT_CELL1_POS@327.519deg), P_CELL_TAB_POS1.1, R_BAT1_ISO1.1
BAT_CELL2_POS: J_CAST_activation_interface1.7 (BAT_CELL2_POS@32.481deg), J_CAST_power_board1.4 (BAT_CELL2_POS@32.481deg), P_CELL_TAB_POS2.1, R_BAT2_ISO1.1
BAT_CELL3_POS: J_CAST_activation_interface1.31 (BAT_CELL3_POS@324.812deg), J_CAST_power_board1.25 (BAT_CELL3_POS@324.812deg), P_CELL_TAB_POS3.1, R_BAT3_ISO1.1
BAT_ISO_DRIVE: J_CAST_companion_compute1.26 (BAT_ISO_DRIVE@75.789deg), J_CAST_power_board1.10 (BAT_ISO_DRIVE@75.789deg), R_ISO_EN_S1.1, U_MPU1.F14 (PE6)
BAT_ISO_EN: Q_ISO_DRV1.1 (G), Q_ISO_USB1.3 (D), R_ISO_EN_PD1.1, R_ISO_EN_S1.2
BAT_ISO_G: Q_ISO1.3 (G), R_ISO_H1.2, R_ISO_L1.1
BAT_ISO_GD: Q_ISO_DRV1.3 (D), R_ISO_L1.2
BAT_ISO_USBG: Q_ISO_USB1.1 (G), R_ISO_USB_H1.2, R_ISO_USB_L1.1
BAT_PROT: CBAT1.1 (+), CBAT2.1 (+), CBAT3.1, C_AWR_BUCK_IN1_1.1, C_AWR_BUCK_IN1_2.1, C_AWR_BUCK_IN1_3.1, C_AWR_BUCK_IN1_4.1, C_AWR_BUCK_IN1_5.1, C_AWR_BUCK_IN2.1, C_IR_TX1.1, D_IR_TX1.2 (A), J_CAST_activation_interface1.1 (BAT_PROT@0deg), J_CAST_aft_end_board1.1 (BAT_PROT@0deg), J_CAST_power_board1.1 (BAT_PROT@0deg), J_CAST_radar_module1.1 (BAT_PROT@0deg), J_CAST_wakeup_board1.1 (BAT_PROT@0deg), QMAIN1.2 (S), Q_ISO1.4 (S), Q_USB_OR1.4 (S), R_ISO_H1.1, R_USBOR_H1.1, TP_BAT1.1, TP_BAT_PROT1.1, U_ACTIVATE_DEC1.1 (~LE), U_ACTIVATE_DEC1.24 (VCC), U_AWR_BUCK12.5 (VIN), U_AWR_BUCK13.5 (VIN), U_AWR_LDO18.6 (VIN)
BAT_RAW: C_AON_IN1.1, C_BAT_BULK1.1, C_BAT_BULK2.1, J_CAST_aft_end_board1.11 (BAT_RAW@27.068deg), J_CAST_power_board1.2 (BAT_RAW@27.068deg), J_CAST_wakeup_board1.2 (BAT_RAW@27.068deg), Q_AON_EN1.2 (S), Q_ISO1.1 (D_1), Q_ISO1.2 (D_2), Q_ISO1.5 (D_3), Q_ISO1.6 (D_4), RAON_PU1.1, RMAIN_PU1.1, R_BAT1_ISO1.2, R_BAT2_ISO1.2, R_BAT3_ISO1.2, R_JUMP_PU1.1, TP_BAT_RAW1.1, U_AON_LDO1.1 (IN), U_TMR_LDO1.1 (IN), U_TMR_LDO1.3 (EN)
BLE_ANT: C_BLE_DCBLK1.2, U_ANTSW_S1.3 (RF1)
BLE_RF: C_BLE_DCBLK1.1, C_WBA_PI2.1, L_WBA_PI1.2
BOOST_FB: R_BOOST_FB1.2, R_BOOST_FB2.1, U_BOOST1.4 (VFB)
BOOST_OUT: CBOOST_OUT1.1 (+), CBOOST_OUT2.1, R_BOOST_FB1.1, U_BOOST1.5 (VOUT), U_PWR1.1 (EN), U_PWR1.6 (VIN)
BOOST_SW: L_PWR1.2, U_BOOST1.1 (SW)
BOOT0: J_CAST_aft_end_board1.62 (BOOT0@354.586deg), J_CAST_companion_compute1.79 (BOOT0@354.586deg), R_MPU_BOOT0.2, TP_BOOT0.1, U_MPU1.T2 (BOOT0)
CAM_CSI_CLK_N: J_CAST_camera_module1.10 (CONE:camera_module:CAM_CSI_CLK_N@186.76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), J_CAST_companion_compute1.46 (CONE:camera_module:CAM_CSI_CLK_N@186.76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), U_CAM1.D12 (CLK_N), U_MPU1.C2 (CSI_CKN)
CAM_CSI_CLK_P: J_CAST_camera_module1.9 (CONE:camera_module:CAM_CSI_CLK_P@170.52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), J_CAST_companion_compute1.40 (CONE:camera_module:CAM_CSI_CLK_P@170.52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), U_CAM1.D11 (CLK_P), U_MPU1.C1 (CSI_CKP)
CAM_CSI_D0_N: J_CAST_camera_module1.11 (CONE:camera_module:CAM_CSI_D0_N@189.474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), J_CAST_companion_compute1.47 (CONE:camera_module:CAM_CSI_D0_N@189.474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), U_CAM1.C10 (DATA0_N), U_MPU1.E1 (CSI_D0N)
CAM_CSI_D0_P: J_CAST_camera_module1.8 (CONE:camera_module:CAM_CSI_D0_P@167.82d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), J_CAST_companion_compute1.39 (CONE:camera_module:CAM_CSI_D0_P@167.82d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), U_CAM1.C9 (DATA0_P), U_MPU1.E2 (CSI_D0P)
CAM_CSI_D1_N: J_CAST_camera_module1.12 (CONE:camera_module:CAM_CSI_D1_N@192.18d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), J_CAST_companion_compute1.48 (CONE:camera_module:CAM_CSI_D1_N@192.18d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), U_CAM1.C11 (DATA1_N), U_MPU1.D2 (CSI_D1N)
CAM_CSI_D1_P: J_CAST_camera_module1.7 (CONE:camera_module:CAM_CSI_D1_P@165.113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), J_CAST_companion_compute1.38 (CONE:camera_module:CAM_CSI_D1_P@165.113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), U_CAM1.C12 (DATA1_P), U_MPU1.D1 (CSI_D1P)
CAM_EXTCLK: J_CAST_camera_module1.13 (CONE:camera_module:CAM_EXTCLK@194.887deg), J_CAST_companion_compute1.49 (CONE:camera_module:CAM_EXTCLK@194.887deg), U_CAM1.G11 (EXTCLK), U_MPU1.K9 (PA8)
CAM_NRST: U_CAM1.F7 (RESET_BAR)
CAM_PHY_REG: C_CAM_PHY_REG1.1, U_CAM1.F12 (CAP_1UF_PHY)
CAM_RSVD: R_CAM_RSVD1.1, U_CAM1.F10 (RSVD)
CAM_SCL: U_CAM1.F6 (SCLK)
CAM_SDA: U_CAM1.E6 (SDATA)
COMP_0V9: C_PMIC_0V9_1.1, C_PMIC_0V9_2.1, J_CAST_companion_compute1.28 (COMP_0V9@81.203deg), J_CAST_power_board1.12 (COMP_0V9@81.203deg), L_PMIC_BUCK1.2, U_MPU1.E13 (VDDCPU_1), U_MPU1.G13 (VDDCPU_2), U_MPU1.J13 (VDDCPU_3), U_MPU1.L13 (VDDCPU_4), U_MPU1.M13 (VDDCPU_5), U_PMIC1.42 (VOUT1)
COMP_0V82: C_MPU_0V82_1.1, C_MPU_0V82_2.1, C_MPU_0V82_BULK1.1, C_PMIC_0V82_1.1, C_PMIC_0V82_2.1, J_CAST_companion_compute1.27 (COMP_0V82@78.496deg), J_CAST_power_board1.11 (COMP_0V82@78.496deg), L_PMIC_BUCK5.2, U_MPU1.B1 (VDDCSI), U_MPU1.C6 (VDDDSI), U_MPU1.G10 (VDDCORE_1), U_MPU1.H11 (VDDCORE_2), U_MPU1.J1 (VDDLVDS), U_MPU1.J10 (VDDCORE_3), U_MPU1.K11 (VDDCORE_4), U_MPU1.L10 (VDDCORE_5), U_MPU1.M11 (VDDGPU_1), U_MPU1.N8 (VDDCORE_6), U_MPU1.N10 (VDDCORE_7), U_MPU1.N14 (VDDGPU_2), U_MPU1.P11 (VDDGPU_3), U_MPU1.P13 (VDDGPU_4), U_MPU1.R10 (VDDGPU_5), U_MPU1.T14 (VDDCOMBOPHY), U_MPU1.U12 (VDDPCIECLK), U_MPU1.W16 (VDDCOMBOPHYTX), U_PMIC1.35 (VOUT5)
COMP_1V2: C_CAM_LDO_VDD_OUT1.1, C_CAM_VDD_1.1, C_CAM_VDD_BULK1.1, C_DDR_BULK1_1.1, C_DDR_BULK1_2.1, C_DDR_BULK1_3.1, C_DDR_BULK1_4.1, C_DDR_BULK1_5.1, C_DDR_BULK2_1.1, C_DDR_BULK2_2.1, C_DDR_BULK2_3.1, C_DDR_BULK2_4.1, C_DDR_BULK2_5.1, C_DDR_VDD1.1, C_DDR_VDD2.1, C_DDR_VDD3.1, C_DDR_VDD4.1, C_DDR_VDD5.1, C_DDR_VDD6.1, C_MPU_QDDR_1.1, C_MPU_QDDR_2.1, C_PMIC_1V2_1_1.1, C_PMIC_1V2_1_2.1, C_PMIC_1V2_1_3.1, C_PMIC_1V2_1_4.1, C_PMIC_1V2_1_5.1, C_PMIC_1V2_2.1, J_CAST_camera_module1.6 (CONE:camera_module:COMP_1V2@162.406deg), J_CAST_companion_compute1.29 (COMP_1V2@83.91deg), J_CAST_companion_compute1.37 (CONE:camera_module:COMP_1V2@162.406deg), J_CAST_power_board1.13 (COMP_1V2@83.91deg), L_PMIC_BUCK6.2, R_DDR_ALERTN_PU1.2, R_DDR_VREFCA_TOP1.1, U_CAM1.A4 (VDD), U_CAM1.A8 (VDD), U_CAM1.A12 (VDD), U_CAM1.B10 (VDD), U_CAM1.C8 (VDD_PHY), U_CAM1.D7 (VDD), U_CAM1.E1 (VDD), U_CAM1.F11 (VDD_DATA), U_CAM1.G8 (VDD), U_CAM_LDO_VDD1.5 (OUT), U_DDR4.A1 (VDDQ_1), U_DDR4.A9 (VDDQ_2), U_DDR4.B3 (VDD_1), U_DDR4.B9 (VDD_2), U_DDR4.C1 (VDDQ_3), U_DDR4.D1 (VDD_3), U_DDR4.D9 (VDDQ_4), U_DDR4.F2 (VDDQ_5), U_DDR4.F8 (VDDQ_6), U_DDR4.G1 (VDDQ_7), U_DDR4.G7 (VDD_4), U_DDR4.G9 (VDDQ_8), U_DDR4.J1 (VDD_5), U_DDR4.J2 (VDDQ_9), U_DDR4.J8 (VDDQ_10), U_DDR4.J9 (VDD_6), U_DDR4.L1 (VDD_7), U_DDR4.L9 (VDD_8), U_DDR4.R1 (VDD_9), U_DDR4.T9 (VDD_10), U_MPU1.F16 (VDDQDDR_1), U_MPU1.J16 (VDDQDDR_2), U_MPU1.L16 (VDDQDDR_3), U_MPU1.M16 (VDDQDDR_4), U_MPU1.P16 (VDDQDDR_5), U_MPU1.T16 (VDDQDDR_6), U_PMIC1.46 (VOUT6)
COMP_1V8: C_CAM_VDD1.1, C_CAM_VDDIO_1.1, C_CAM_VDDIO_BULK1.1, C_MPU_18A_1.1, C_MPU_18A_2.1, C_PMIC_1V8_1.1, C_PMIC_1V8_2.1, C_USB_18.1, J_CAST_camera_module1.14 (CONE:camera_module:COMP_1V8@197.594deg), J_CAST_companion_compute1.18 (COMP_1V8@51.429deg), J_CAST_companion_compute1.50 (CONE:camera_module:COMP_1V8@197.594deg), J_CAST_power_board1.6 (COMP_1V8@51.429deg), J_CAST_wakeup_board1.6 (COMP_1V8@51.429deg), L_PMIC_BUCK4.2, U_CAM1.A7 (VDD_IO), U_CAM1.B4 (VDD_IO), U_CAM1.B5 (VDD_IO), U_CAM1.B11 (VDD_IO), U_CAM1.D3 (VDD_IO), U_CAM1.D6 (VDD_IO), U_CAM1.D10 (VDDIO_PHY), U_CAM1.F1 (VDD_IO), U_CAM1.G12 (VDD_IO), U_MPU1.C5 (VDDA18DSI), U_MPU1.D3 (VDDA18CSI), U_MPU1.D16 (VDDA18DDR), U_MPU1.E15 (VDDA18PLL1), U_MPU1.G6 (VDDA18PLL2), U_MPU1.H6 (VDDA18PLL3), U_MPU1.J4 (VDDA18LVDS), U_MPU1.N5 (VDDA18AON), U_MPU1.N6 (VDDA18ADC), U_MPU1.R13 (VDDA18COMBOPHY), U_MPU1.T13 (VDDA18USB), U_MPU1.U2 (VREF+), U_PMIC1.17 (VOUT4)
COMP_2V8: C_CAM_LDO_VAA_OUT_1.1, C_CAM_LDO_VAA_OUT_2.1, C_CAM_VAA_1.1, C_CAM_VAA_BULK1.1, C_PMIC_2V8_1_1.1, C_PMIC_2V8_1_2.1, C_PMIC_2V8_2.1, J_CAST_camera_module1.5 (CONE:camera_module:COMP_2V8@159.699deg), J_CAST_companion_compute1.36 (CONE:camera_module:COMP_2V8@159.699deg), J_CAST_companion_compute1.54 (COMP_2V8@276.09deg), J_CAST_power_board1.21 (COMP_2V8@276.09deg), U_CAM1.A10 (VAA), U_CAM1.B1 (VAA), U_CAM1.B8 (VAA_PIX), U_CAM1.C2 (VAA_PIX), U_CAM1.F8 (VAA_PHY), U_CAM1.G1 (VAA_PIX), U_CAM1.G2 (VAA), U_CAM1.G7 (VAA), U_CAM1.G9 (VAA_PIX), U_CAM_LDO_VAA1.5 (OUT), U_PMIC1.7 (LDO5OUT)
COMP_3V3: C_AWR_FLASH_VCC1.1, C_MPU_33_1.1, C_MPU_33_2.1, C_MPU_33_3.1, C_MPU_33_4.1, C_MPU_33_5.1, C_MPU_33b1.1, C_MPU_HSE_VDD1.1, C_MPU_LSE_VDD1.1, C_NAND_A_BULK1.1, C_NAND_A_VCC1.1, C_NAND_B_BULK1.1, C_NAND_B_VCC1.1, C_PMIC_3V3_1.1, C_PMIC_3V3_2.1, C_USB_33.1, J_CAST_companion_compute1.70 (COMP_3V3@330.226deg), J_CAST_power_board1.27 (COMP_3V3@330.226deg), J_CAST_radar_module1.19 (COMP_3V3@330.226deg), L_PMIC_BUCK2.2, R_AWR_DRDY_PU1.1, R_AWR_FAULT_PU1.1, R_AWR_NERRIN_PU1.1, R_AWR_NRST1.1, R_AWR_SOP0.1, R_AWR_WARMRST_PU1.1, R_MPU_NRST1.1, R_TMP1_ALERT_PU1.1, R_USB_VBUS_PD1.1, U_AWR1.H1 (VIOIN_1), U_AWR1.V9 (VIOIN_2), U_AWR_FLASH1.3 (WP#/SIO2), U_AWR_FLASH1.7 (RESET#/HOLD#/SIO3), U_AWR_FLASH1.8 (VDD), U_MPU1.D6 (VDDIO4_1), U_MPU1.D10 (VDDIO1), U_MPU1.E6 (VDDIO4_2), U_MPU1.E10 (VDDIO3_1), U_MPU1.F8 (VDDIO2), U_MPU1.F10 (VDDIO3_2), U_MPU1.H8 (VDD_1), U_MPU1.K8 (VDD_2), U_MPU1.L6 (VDD_3), U_MPU1.R6 (VBAT), U_MPU1.R14 (VDD33USB), U_MPU1.U11 (VDD33UCPD), U_NAND_A1.8 (VCC), U_NAND_B1.8 (VCC), U_PMIC1.28 (VOUT2), Y_MPU_HSE1.1 (STANDBY#), Y_MPU_HSE1.4 (VDD), Y_MPU_LSE1.4 (VDD)
COMP_5V: C_ACTIVATE_IN_1.1, C_ACTIVATE_IN_2.1, C_ACTIVATE_IN_3.1, C_ACTIVATE_IN_4.1, C_ACTIVATE_IN_5.1, C_CAM_LDO_VAA_IN1.1, C_CAM_LDO_VDD_IN1.1, C_CAN_GW1.1, C_MPU_5V2.1, C_MPU_5V_1.1, C_MPU_5V_2.1, C_MPU_5V_3.1, C_MPU_5V_4.1, C_MPU_5V_5.1, C_PMIC_5V_FILT_1.1, C_PMIC_5V_FILT_2.1, C_PMIC_5V_FILT_3.1, C_PMIC_5V_FILT_4.1, C_PMIC_5V_FILT_5.1, C_PMIC_VIN1.1, C_PMIC_VIN2.1, C_PMIC_VIN3.1, C_PMIC_VIN4.1, C_PMIC_VIN5.1, C_PMIC_VIN6.1, J_CAST_activation_interface1.6 (COMP_5V@29.774deg), J_CAST_companion_compute1.11 (COMP_5V@29.774deg), J_CAST_fin_ble_board1.3 (COMP_5V@29.774deg), J_CAST_power_board1.3 (COMP_5V@29.774deg), L_ACTIVATE1.1, L_PMIC_FILT1.2, U_ACTIVATE_BOOST1.3 (VIN), U_ACTIVATE_BOOST1.4 (EN), U_CAM_LDO_VAA1.1 (IN), U_CAM_LDO_VAA1.3 (EN), U_CAM_LDO_VDD1.1 (IN), U_CAM_LDO_VDD1.3 (EN), U_CAN_GW1.3 (VCC), U_PMIC1.3 (LDO78IN), U_PMIC1.6 (LDO56IN), U_PMIC1.11 (VIN), U_PMIC1.15 (LDO12IN), U_PMIC1.20 (BUCK4IN), U_PMIC1.24 (BUCK3IN), U_PMIC1.25 (BUCK2IN), U_PMIC1.38 (BUCK5IN), U_PMIC1.39 (BUCK1IN), U_PMIC1.43 (LDO3IN), U_PMIC1.44 (LDO3OUT), U_PMIC1.49 (BUCK6IN), U_PMIC1.50 (BUCK7IN)
COMP_5V_COMP: R_BOOST_COMP1.1, U_COMP_BOOST1.8 (COMP)
COMP_5V_COMP_C: C_BOOST_COMP1.1, R_BOOST_COMP1.2
COMP_5V_FB: R_BOOST_R1.2, R_BOOST_R2.1, U_COMP_BOOST1.9 (FB)
COMP_5V_FREQ: R_BOOST_FREQ1.1, U_COMP_BOOST1.10 (FREQ)
COMP_5V_RAW: C_BOOST_OUT1.1, C_BOOST_OUT2_1.1, C_BOOST_OUT2_2.1, C_BOOST_OUT2_3.1, C_BOOST_OUT2_4.1, C_BOOST_OUT2_5.1, C_BOOST_OUT3.1, C_FIN1_VM1.1, C_FIN2_VM1.1, C_FIN3_VM1.1, C_FIN4_VM1.1, C_FIN_VM_BULK_1.1, C_FIN_VM_BULK_2.1, C_FIN_VM_BULK_3.1, C_FIN_VM_BULK_4.1, C_FIN_VM_BULK_5.1, D_BOOST_COMP1.3 (K), J_CAST_fin_ble_board1.24 (COMP_5V_RAW@278.797deg), J_CAST_power_board1.22 (COMP_5V_RAW@278.797deg), L_PMIC_FILT1.1, R_BOOST_R1.1, U_FIN1.1 (VM), U_FIN2.1 (VM), U_FIN3.1 (VM), U_FIN4.1 (VM)
COMP_5V_SS: C_BOOST_SS1.1, U_COMP_BOOST1.5 (SS)
COMP_5V_SW: D_BOOST_COMP1.1 (A_1), D_BOOST_COMP1.2 (A_2), L_BOOST_COMP1.2, U_COMP_BOOST1.1 (SW_1), U_COMP_BOOST1.2 (SW_2)
COMP_HSE_IN: U_MPU1.R1 (OSC_IN), Y_MPU_HSE1.3 (OUT)
COMP_INM: R_THR1.2, R_THR2.1, U_COMP_PZ1.3 (IN-)
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
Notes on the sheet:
activation_interface
Rail decoupling - no pin declared
aft_end_board
SPI
FIN 1
FIN 3
FIN 2
FIN 4
CAN
BAT
PARACHUTE WIRES
GROUND
PARACHUTE CUTTER
HALL
I2C
JUMPSTART
PROGRAM_MP25
GPIO
camera_module
companion_compute
fin_ble_board
nose_cap
power_board
qpd_module
radar_module
wakeup_board

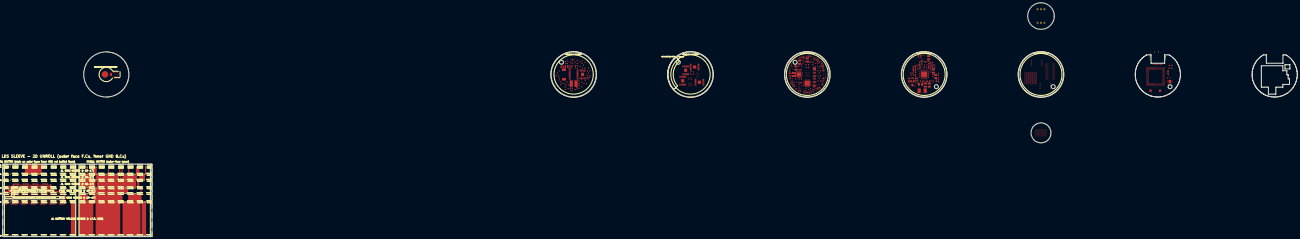
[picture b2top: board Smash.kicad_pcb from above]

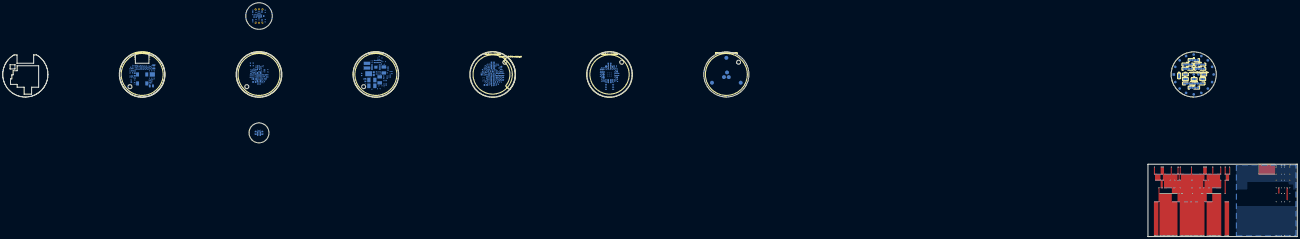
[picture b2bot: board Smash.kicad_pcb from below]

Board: 14 copper layers, 975.0 x 176.1 mm, 688 parts (425 on the bottom side), 433 nets.

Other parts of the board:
MH1, MH1#2, MH1#3, MH1#4, MH1#5, MH1#6: smash_mech_potting
